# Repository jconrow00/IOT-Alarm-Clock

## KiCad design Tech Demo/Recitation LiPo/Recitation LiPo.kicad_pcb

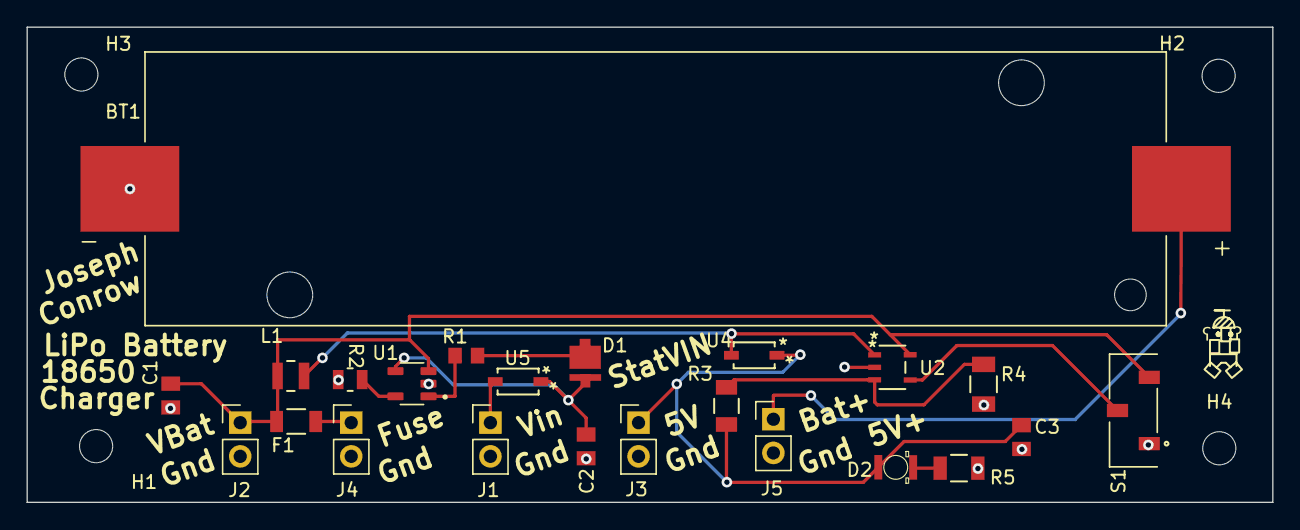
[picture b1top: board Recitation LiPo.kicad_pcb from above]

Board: 2 copper layers, 94.0 x 35.9 mm, 27 parts (0 on the bottom side), 14 nets.

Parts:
BT1: 1042P
C1, C2, C3: 4.7uF; GRM219R6YA475KA73D
D1: Yellow; KW DSLP31.CC-GXHX-4J8K-Z444-60-R18
D2: Red; LTST-C930KRKT
F1: 630mA; FUS1206_24N_SCH
H1, H2, H3, H4: MountingHole; MountingHole_2.5mm
J1, J2, J3, J4, J5: Conn_01x02_Pin; PinHeader_1x02_P2.54mm_Vertical
L1: 10uH; IND_DFE252012C_MUR
R1: 470; RC0805N_YAG
R2: 2K; RES_1220_SUS
R3: 100k; RC1206N_PAN
R4: 33k; RES_RMCF1206_STP
R5: 560; STA_RMCF1206_STP
S1: SPDT; SW_JS102011JCQN
U1: IC BATT CTRL; MCP73832T_2DCI_OT
U2: IC REG BOOST; SOT-23-5_DIO
U4, U5: SCHOTTKY; 1N5819HW-7-F_DIO

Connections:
5V: C3.2, D2.2 (A), J3.1, R3.1, U4.1 (-)
GND: BT1.N, C1.2, C2.1, C3.1, J1.2, J2.2, J3.2, J4.2, J5.2, R2.1, R4.2, R5.2, S1.1, U1.2 (V_{SS}), U2.2 (GND)
unnamed: C2.2, D1.2 (A), U1.4 (V_{DD}), U5.1 (-)
unnamed: D1.1 (K), R1.1
unnamed: D2.1 (K), R5.1
unnamed: F1.1, J4.1
unnamed: BT1.P, J5.1
unnamed: R2.2, U1.5 (PROG)
unnamed: R1.2, U1.1 (STAT)
unnamed: R3.2, R4.1, U2.3 (FB)
unnamed: L1.1, U2.1 (SW), U4.2 (+)
unnamed: S1.2, U2.4 (~SHDN)
V_{BAT}: C1.1, F1.2, J2.1, L1.2, S1.3, U1.3 (V_{BAT}), U2.5 (IN)
V_{IN}: J1.1, U5.2 (+)

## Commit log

2024-04-26 add_poster
2024-04-26 update2
2024-05-01 update4.30
2024-05-01 alarm_working
2024-05-03 working_code_and_buttons
2024-05-06 working_all_revised5_5
2024-05-06 up_one
2024-05-14 update_since_final
2024-06-07 test update
2024-06-17 final_commit
